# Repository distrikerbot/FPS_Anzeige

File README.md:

# FPS_Anzeige
First folder cllaed FPS_Anzeige is the python code with reading out the dll from msi afterburner

todo:
finish PCB and Code

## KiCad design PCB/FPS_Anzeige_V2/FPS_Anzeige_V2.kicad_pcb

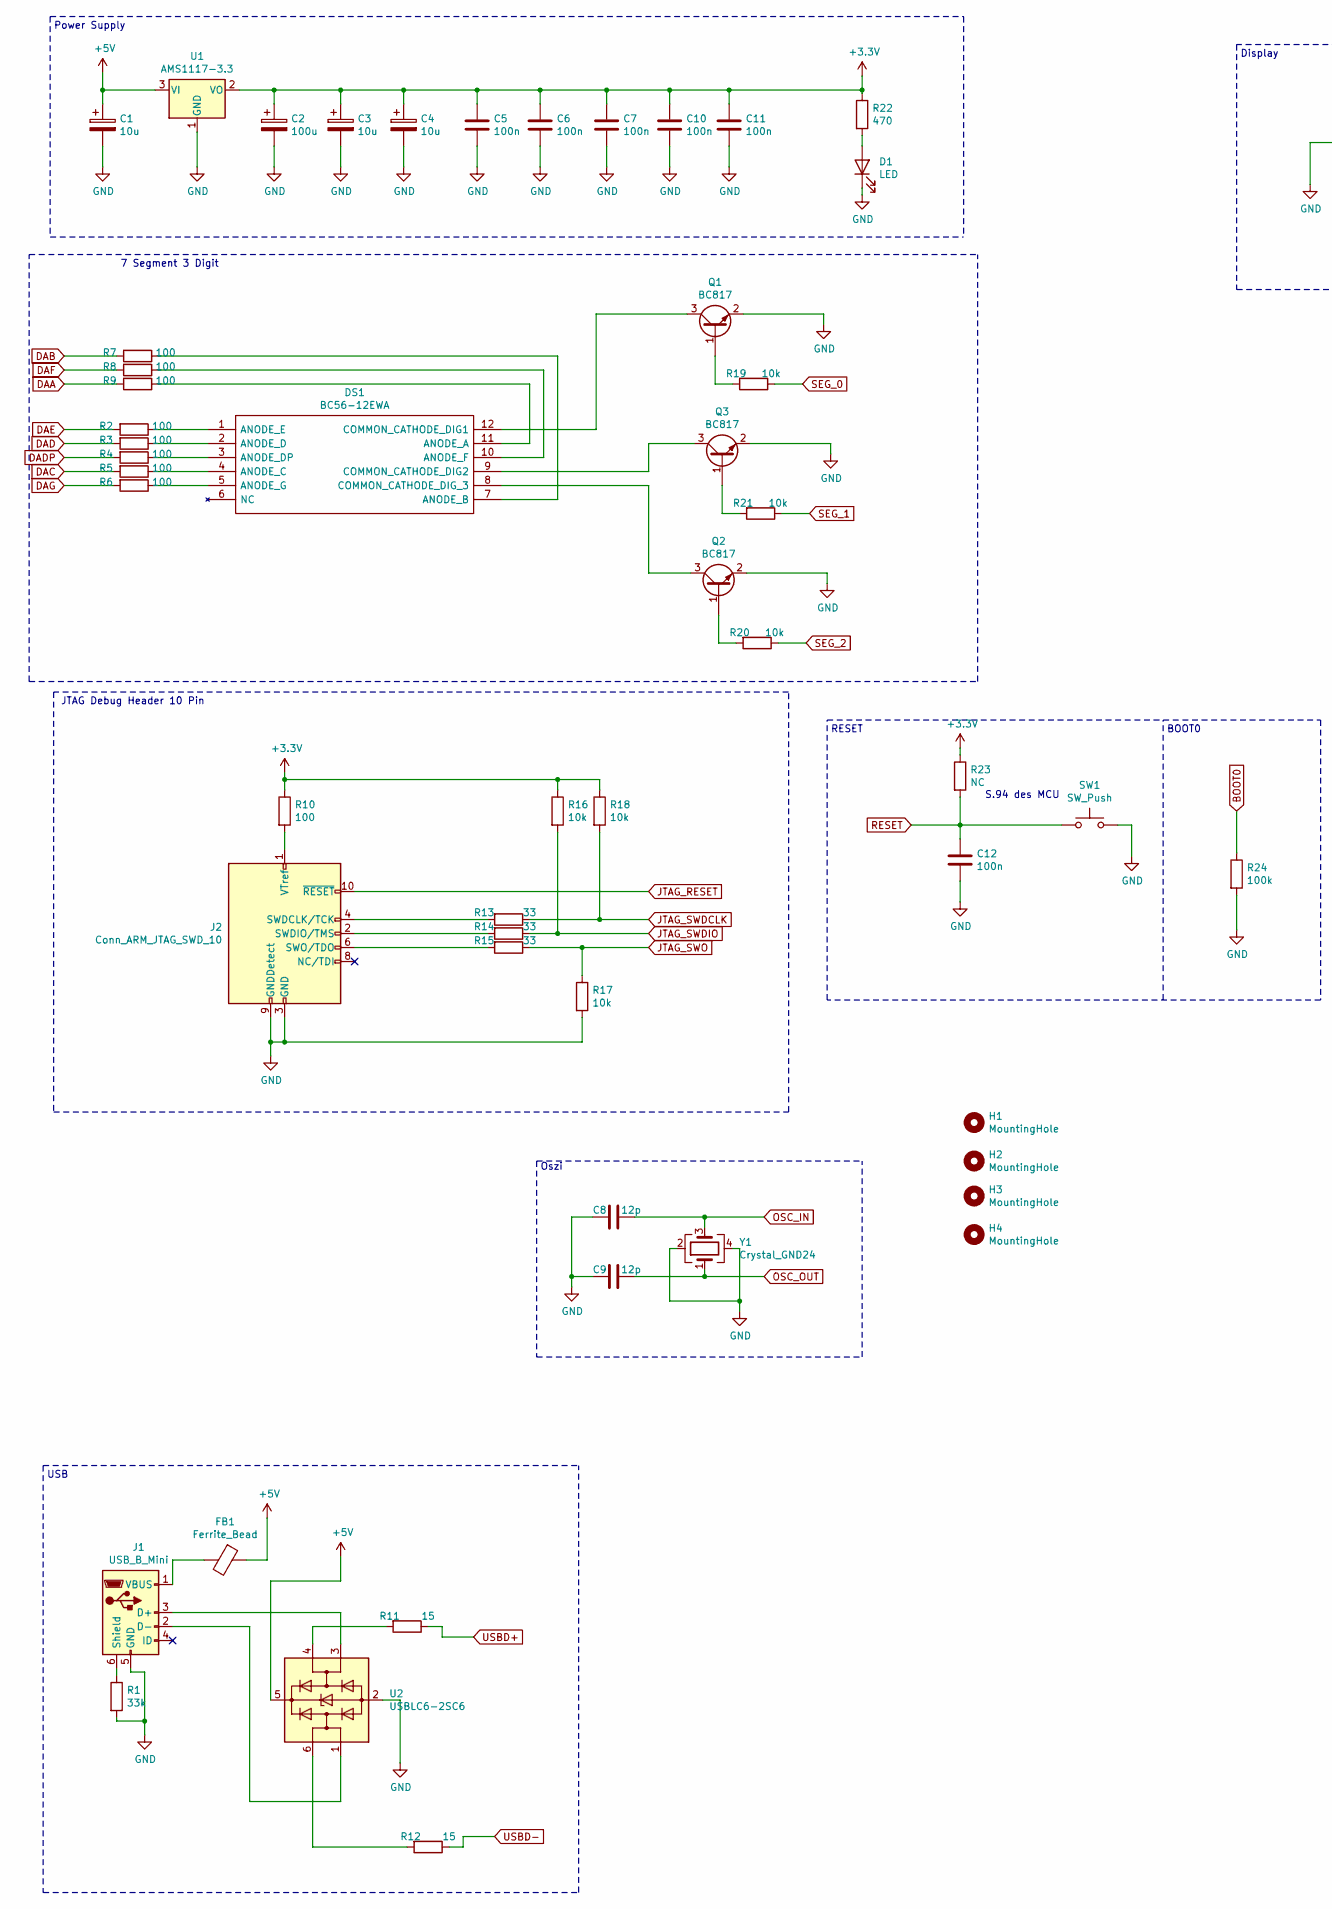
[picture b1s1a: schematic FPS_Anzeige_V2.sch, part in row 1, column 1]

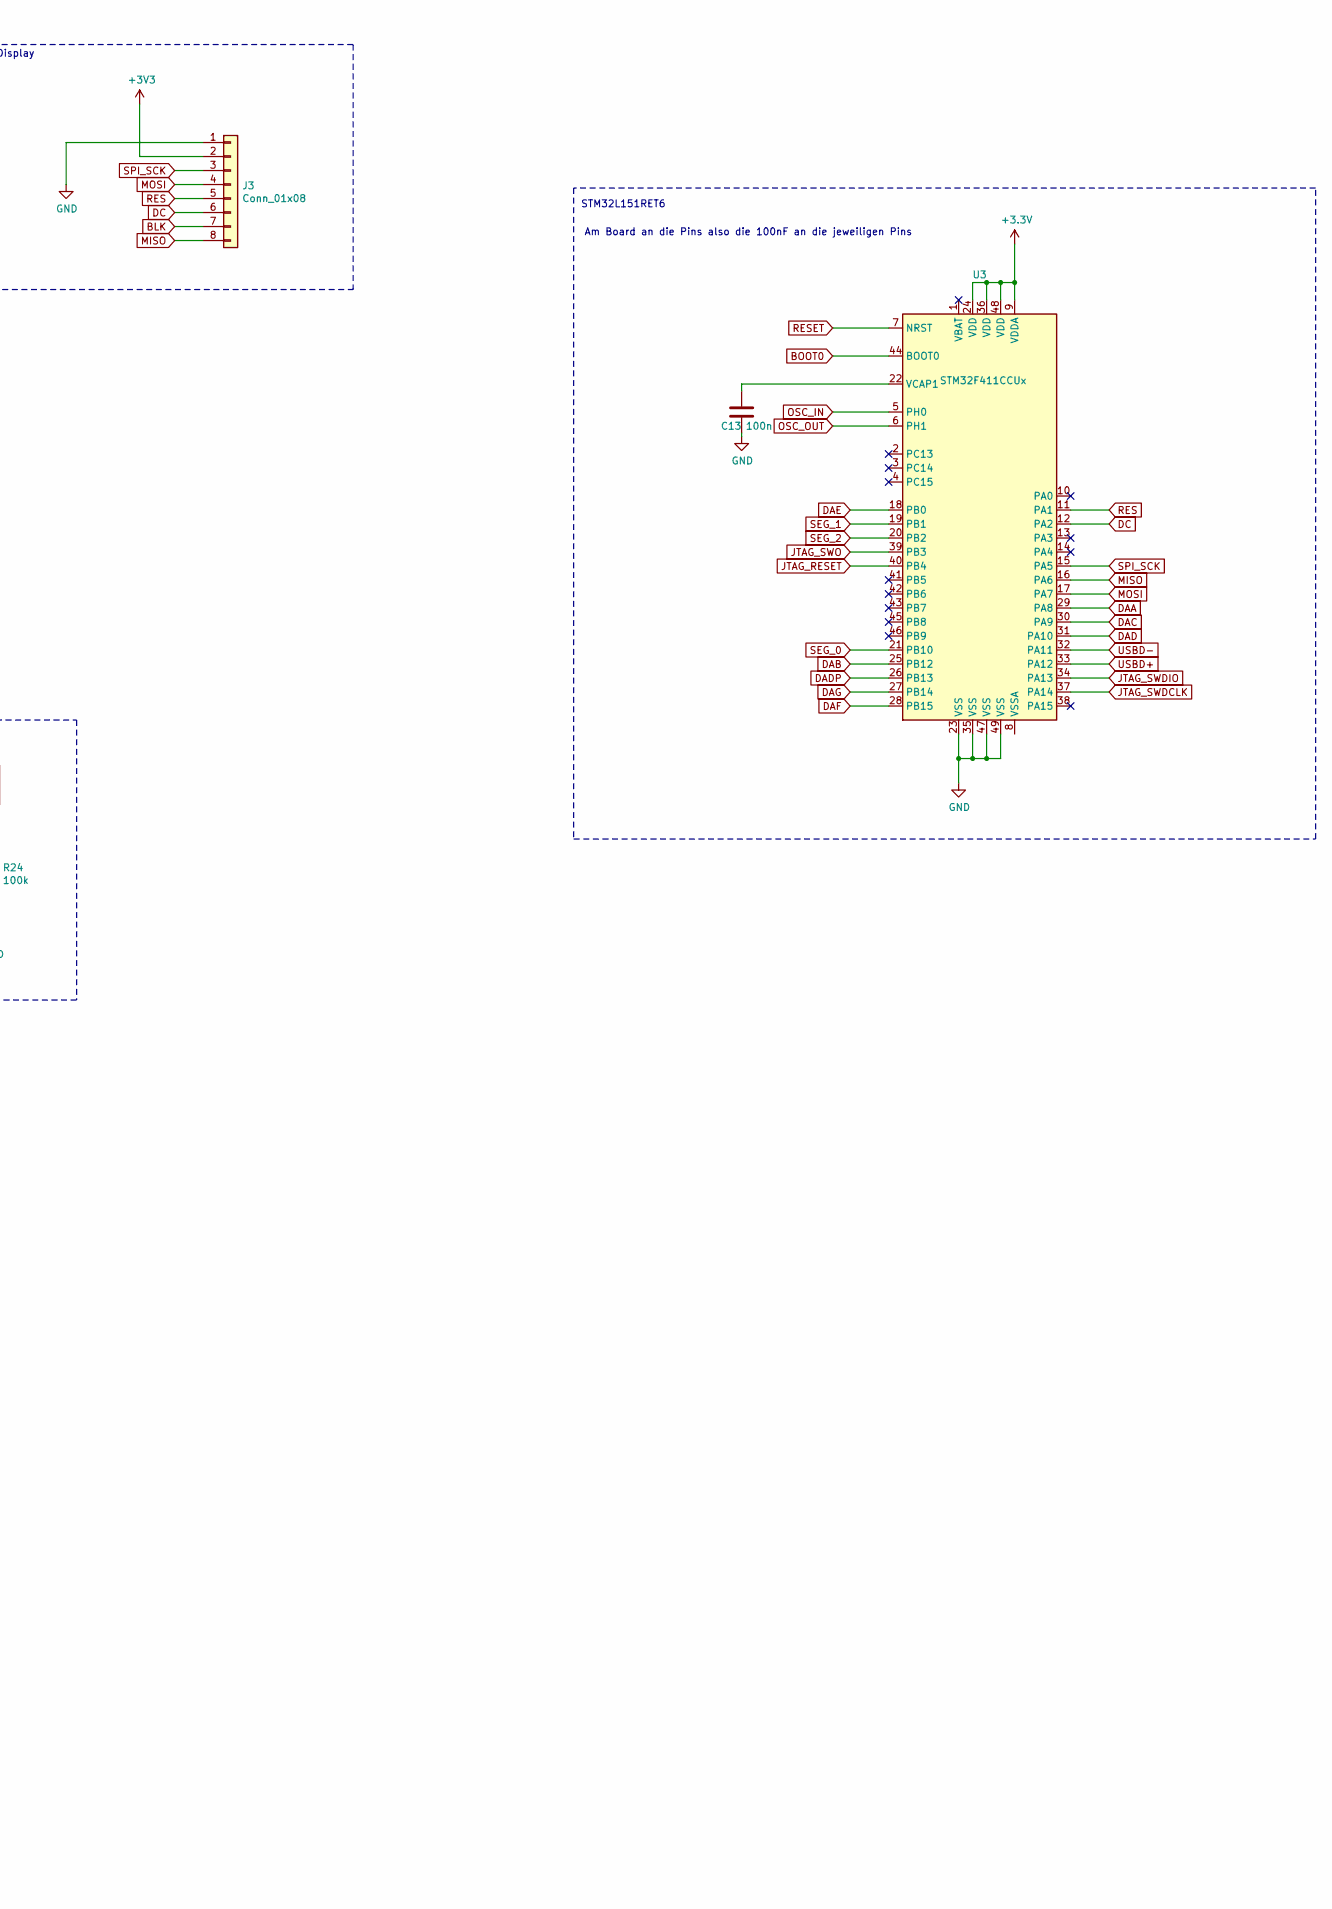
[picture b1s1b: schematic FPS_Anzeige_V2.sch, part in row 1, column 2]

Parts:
C1, C3, C4: 10u; CP_Elec_4x4.5
C2: 100u; CP_Elec_5x5.3
C5, C6, C7, C10, C11, C12, C13: 100n; C_0805_2012Metric_Pad1.18x1.45mm_HandSolder
C8, C9: 12p; C_0805_2012Metric_Pad1.18x1.45mm_HandSolder
D1: LED; LED_0805_2012Metric
DS1: BC56-12EWA; DIPS1524W50P254L3760H835Q12N; Mouser Part Number 604-BC56-12EWA
FB1: Ferrite_Bead; R_0805_2012Metric
H1, H2, H3, H4: MountingHole; MountingHole_3.2mm_M3_DIN965
J1: USB_B_Mini; USB_Mini-B_Wuerth_65100516121_Horizontal
J2: Conn_ARM_JTAG_SWD_10; PinHeader_2x05_P1.27mm_Vertical
J3: Conn_01x08; PinSocket_1x08_P2.54mm_Vertical
Q1, Q2, Q3: BC817; SOT-23
R1: 33k; R_0805_2012Metric
R2, R3, R4, R5, R6, R7, R8, R9, R10: 100; R_0805_2012Metric
R11, R12: 15; R_0805_2012Metric
R13, R14, R15: 33; R_0805_2012Metric
R16, R17, R18, R19, R20, R21: 10k; R_0805_2012Metric
R22: 470; R_0805_2012Metric
R23: NC; R_0805_2012Metric
R24: 100k; R_0805_2012Metric
SW1: SW_Push; SW_Push_1P1T_NO_6x6mm_H9.5mm
U1: AMS1117-3.3; SOT-223-3_TabPin2
U2: USBLC6-2SC6; SOT-23-6
U3: STM32F411CCUx; QFN-48-1EP_7x7mm_P0.5mm_EP5.6x5.6mm
Y1: Crystal_GND24; Crystal_SMD_3225-4Pin_3.2x2.5mm

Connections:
+5V: C1.1, FB1.1, U1.3 (VI), U2.5 (VBUS)
BOOT0: R24.1, U3.44 (BOOT0)
DAA: R9.2, U3.29 (PA8)
DAB: R7.2, U3.25 (PB12)
DAC: R5.2, U3.30 (PA9)
DAD: R3.2, U3.31 (PA10)
DADP: R4.2, U3.26 (PB13)
DAE: R2.2, U3.18 (PB0)
DAF: R8.2, U3.28 (PB15)
DAG: R6.2, U3.27 (PB14)
DC: J3.6, U3.12 (PA2)
GND: C1.2, C2.2, C3.2, C4.2, C5.2, C6.2, C7.2, C8.2, C9.2, C10.2, C11.2, C12.2, C13.2, D1.1 (K), J1.5 (GND), J2.3 (GND), J2.5 (GND), J2.9 (GNDDetect), J3.1, Q1.2 (E), Q2.2 (E), Q3.2 (E), R1.2, R17.2, R24.2, SW1.2, U1.1 (GND), U2.2 (GND), U3.23 (VSS), U3.35 (VSS), U3.47 (VSS), U3.49 (VSS), Y1.2, Y1.4
JTAG_RESET: J2.10 (~RESET~), U3.40 (PB4)
JTAG_SWDCLK: R13.1, R18.2, U3.37 (PA14)
JTAG_SWDIO: R14.1, R16.2, U3.34 (PA13)
JTAG_SWO: R15.1, R17.1, U3.39 (PB3)
MISO: J3.8, U3.16 (PA6)
MOSI: J3.4, U3.17 (PA7)
unnamed: C13.1, U3.22 (VCAP1)
unnamed: D1.2 (A), R22.2
unnamed: DS1.1 (ANODE_E), R2.1
unnamed: DS1.2 (ANODE_D), R3.1
unnamed: DS1.3 (ANODE_DP), R4.1
unnamed: DS1.4 (ANODE_C), R5.1
unnamed: DS1.5 (ANODE_G), R6.1
unnamed: DS1.7 (ANODE_B), R7.1
unnamed: DS1.8 (COMMON_CATHODE_DIG_3), Q2.3 (C)
unnamed: DS1.9 (COMMON_CATHODE_DIG2), Q3.3 (C)
unnamed: DS1.10 (ANODE_F), R8.1
unnamed: DS1.11 (ANODE_A), R9.1
unnamed: DS1.12 (COMMON_CATHODE_DIG1), Q1.3 (C)
unnamed: FB1.2, J1.1 (VBUS)
unnamed: J1.2 (D-), U2.1 (I/O1)
unnamed: J1.3 (D+), U2.3 (I/O2)
unnamed: J1.6 (Shield), R1.1
unnamed: J2.1 (VTref), R10.2
unnamed: J2.2 (SWDIO/TMS), R14.2
unnamed: J2.4 (SWDCLK/TCK), R13.2
unnamed: J2.6 (SWO/TDO), R15.2
unnamed: Q1.1 (B), R19.2
unnamed: Q2.1 (B), R20.2
unnamed: Q3.1 (B), R21.2
unnamed: R11.2, U2.4 (I/O2)
unnamed: R12.2, U2.6 (I/O1)
OSC_IN: C8.1, U3.5 (PH0), Y1.3
OSC_OUT: C9.1, U3.6 (PH1), Y1.1
RES: J3.5, U3.11 (PA1)
RESET: C12.1, R23.2, SW1.1, U3.7 (NRST)
SEG_0: R19.1, U3.21 (PB10)
SEG_1: R21.1, U3.19 (PB1)
SEG_2: R20.1, U3.20 (PB2)
SPI_SCK: J3.3, U3.15 (PA5)
USBD+: R11.1, U3.33 (PA12)
USBD-: R12.1, U3.32 (PA11)

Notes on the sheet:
Oszi
7 Segment 3 Digit
Power Supply
JTAG Debug Header 10 Pin
USB
RESET
BOOT0
Am Board an die Pins also die 100nF an die jeweiligen Pins
STM32L151RET6
S.94 des MCU
Display

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
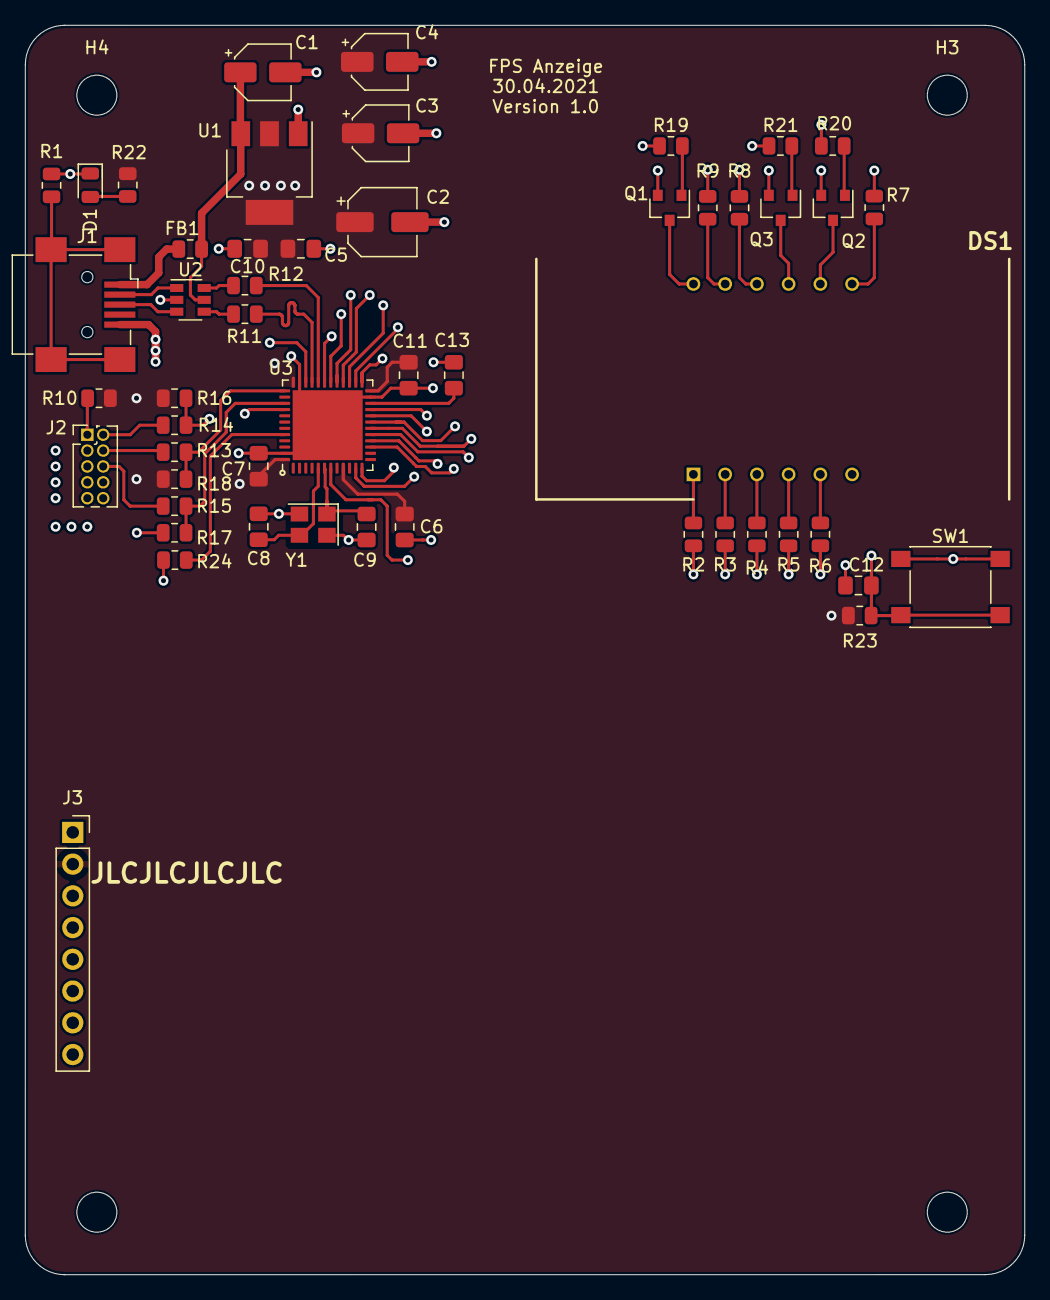
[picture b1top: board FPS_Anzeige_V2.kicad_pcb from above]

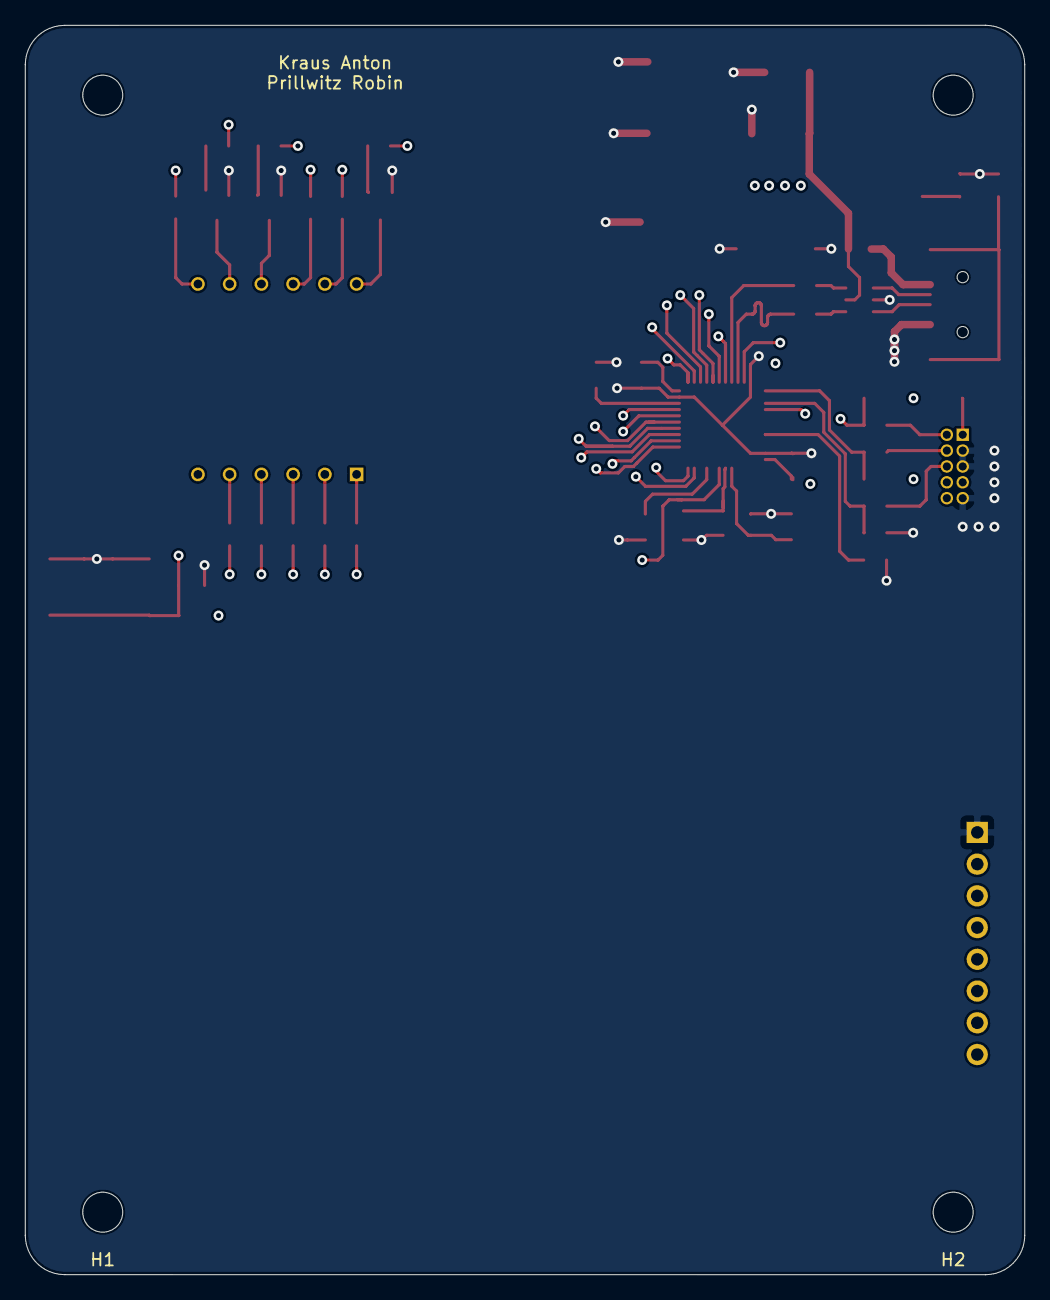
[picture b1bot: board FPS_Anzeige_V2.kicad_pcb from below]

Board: 4 copper layers, 80.0 x 100.0 mm, 55 parts (2 on the bottom side), 55 nets.

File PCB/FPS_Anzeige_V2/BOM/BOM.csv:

"Source:","C:\KiCad\Projekte\FPS_Anzeige_V2\FPS_Anzeige_V2\FPS_Anzeige_V2.sch"
"Date:","23.04.2021 15:09:36"
"Tool:","Eeschema (5.1.9)-1"
"Generator:","C:\Program Files\KiCad\bin\scripting\plugins/bom_csv_grouped_by_value_with_fp.py"
"Component Count:","61"
"Ref","Qnty","Value","Cmp name","Footprint","Description","Vendor"
"C1, C3, C4, ","3","10u","CP","Capacitor_SMD:CP_Elec_4x4.5","Polarized capacitor",""
"C2, ","1","100u","CP","Capacitor_SMD:CP_Elec_5x5.3","Polarized capacitor",""
"C5, C6, C7, C10, C11, C12, C13, ","7","100n","C","Capacitor_SMD:C_0805_2012Metric_Pad1.18x1.45mm_HandSolder","Unpolarized capacitor",""
"C8, C9, ","2","12p","C","Capacitor_SMD:C_0805_2012Metric_Pad1.18x1.45mm_HandSolder","Unpolarized capacitor",""
"D2, ","1","LED","LED","LED_SMD:LED_0805_2012Metric","Light emitting diode",""
"DS1, ","1","BC56-12EWA","BC56-12EWA","SamacSys_Parts:DIPS1524W50P254L3760H835Q12N","LED Displays & Accessories Tri Red 625nm Common Cathode",""
"FB1, ","1","Ferrite_Bead","Ferrite_Bead","Resistor_SMD:R_0805_2012Metric","Ferrite bead",""
"H1, H2, H3, H4, ","4","MountingHole","MountingHole","MountingHole:MountingHole_3.2mm_M3_DIN965","Mounting Hole without connection",""
"J1, ","1","USB_B_Mini","USB_B_Mini","Connector_USB:USB_Mini-B_Wuerth_65100516121_Horizontal","USB Mini Type B connector",""
"J2, ","1","Conn_ARM_JTAG_SWD_10","Conn_ARM_JTAG_SWD_10","Connector_PinHeader_1.27mm:PinHeader_2x05_P1.27mm_Vertical","Cortex Debug Connector, standard ARM Cortex-M SWD and JTAG interface",""
"J3, ","1","Conn_01x07","Conn_01x07","Connector_PinHeader_2.54mm:PinHeader_1x07_P2.54mm_Vertical","Generic connector, single row, 01x07, script generated (kicad-library-utils/schlib/autogen/connector/)",""
"Q1, Q2, Q3, ","3","BC817","BC817","Package_TO_SOT_SMD:SOT-23","0.8A Ic, 45V Vce, NPN Transistor, SOT-23",""
"R1, R2, R3, R4, R5, R6, R7, R8, R11, ","9","100","R","Resistor_SMD:R_0805_2012Metric","Resistor",""
"R9, R10, ","2","15","R","Resistor_SMD:R_0805_2012Metric","Resistor",""
"R12, R13, R14, R26, R27, ","5","33","R","Resistor_SMD:R_0805_2012Metric","Resistor",""
"R15, ","1","33k","R","Resistor_SMD:R_0805_2012Metric","Resistor",""
"R16, R17, R18, R19, R20, R21, ","6","10k","R","Resistor_SMD:R_0805_2012Metric","Resistor",""
"R22, ","1","470","R","Resistor_SMD:R_0805_2012Metric","Resistor",""
"R23, ","1","100k","R","Resistor_SMD:R_0805_2012Metric","Resistor",""
"R24, R25, ","2","4.7k","R","Resistor_SMD:R_0805_2012Metric","Resistor",""
"R28, ","1","NC","R","Resistor_SMD:R_0805_2012Metric","Resistor",""
"R29, R30, ","2","0R","R","Resistor_SMD:R_0805_2012Metric","Resistor",""
"SW1, ","1","SW_Push","SW_Push","Button_Switch_SMD:SW_Push_1P1T_NO_6x6mm_H9.5mm","Push button switch, generic, two pins",""
"U1, ","1","AMS1117-3.3","AMS1117-3.3","Package_TO_SOT_SMD:SOT-223-3_TabPin2","1A Low Dropout regulator, positive, 3.3V fixed output, SOT-223",""
"U2, ","1","STM32L151RETx","STM32L151RETx","Package_QFP:LQFP-64_10x10mm_P0.5mm","ARM Cortex-M3 MCU, 512KB flash, 80KB RAM, 32MHz, 1.65-3.6V, 51 GPIO, LQFP-64",""
"U3, ","1","USBLC6-2SC6","USBLC6-2SC6","Package_TO_SOT_SMD:SOT-23-6","Very low capacitance ESD protection diode, 2 data-line, SOT-23-6",""
"Y1, ","1","Crystal_GND24","Crystal_GND24","Crystal:Crystal_SMD_3225-4Pin_3.2x2.5mm","Four pin crystal, GND on pins 2 and 4",""

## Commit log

2022-01-10 Readme
2022-01-10 Init
    Init Code
2022-01-10 Init
    Init KiCad Project
